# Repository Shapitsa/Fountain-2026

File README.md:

# Fountain-2026
Lutron Competition Submission at SiLab 2026

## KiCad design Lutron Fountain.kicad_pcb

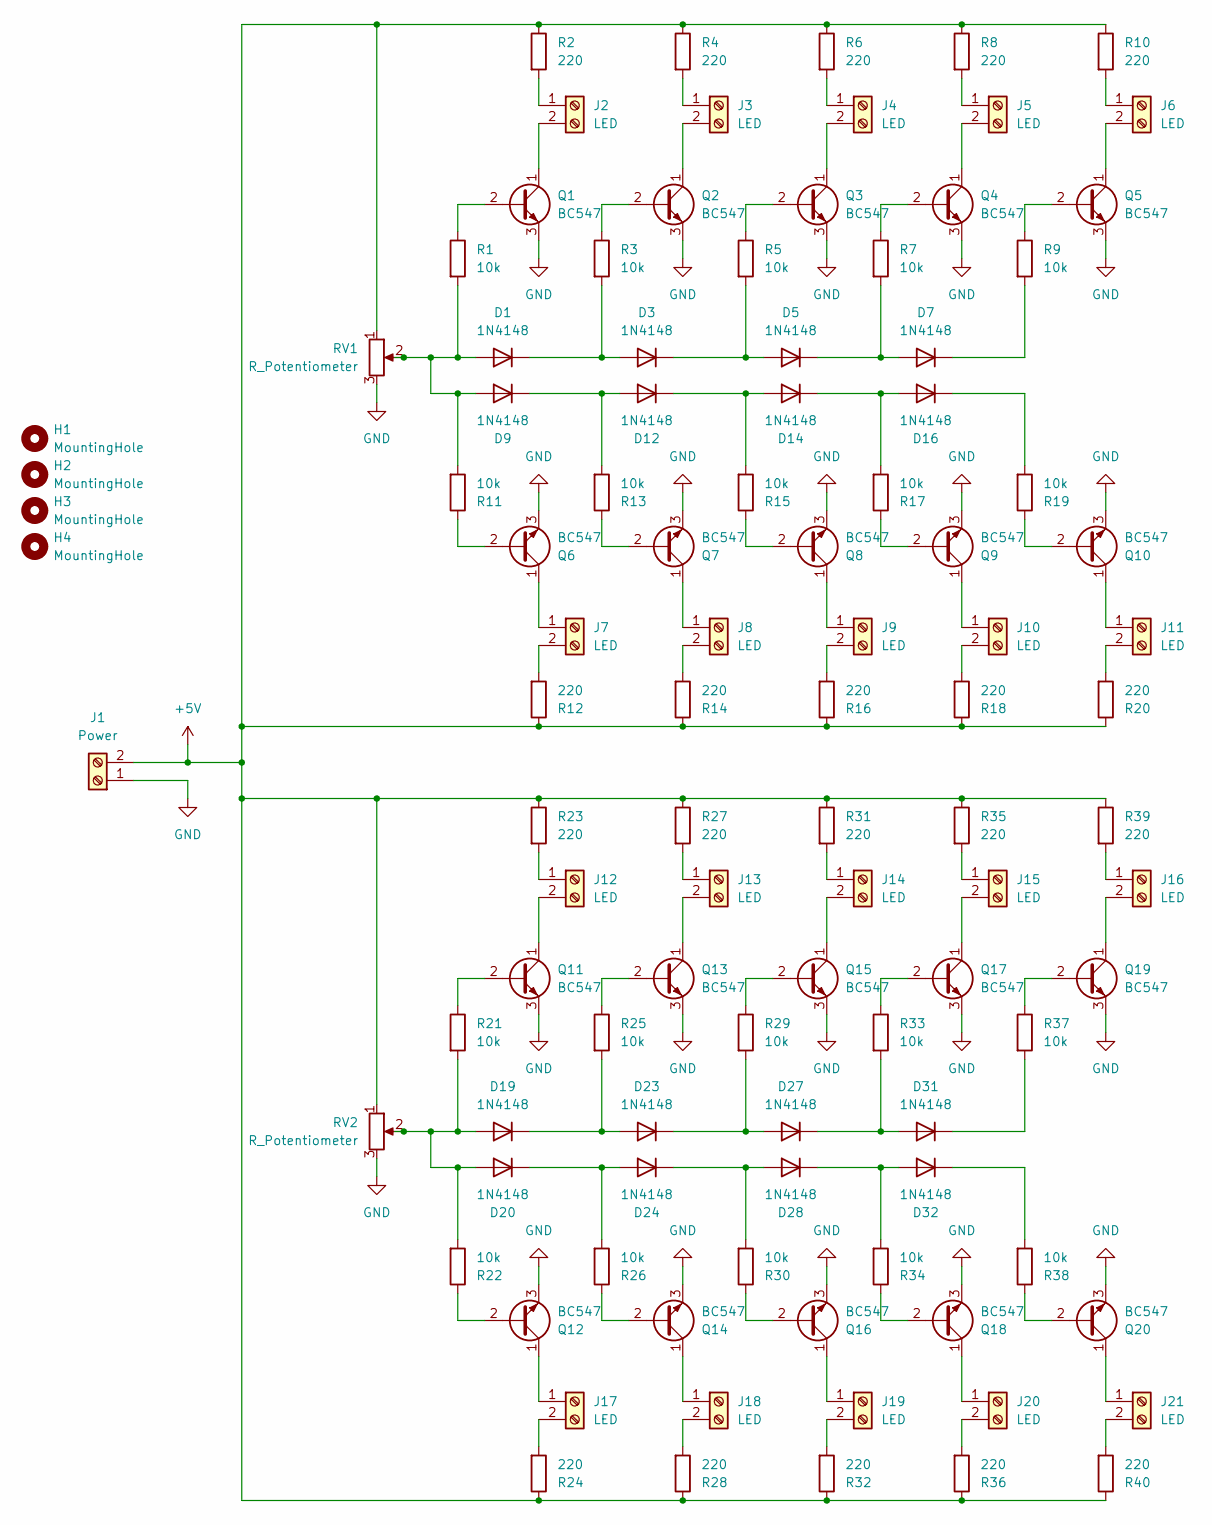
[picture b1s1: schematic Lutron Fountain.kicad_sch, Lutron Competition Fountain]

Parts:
D1, D3, D5, D7, D9, D12, D14, D16, D19, D20, D23, D24, D27, D28, D31, D32: 1N4148; D_DO-35_SOD27_P7.62mm_Horizontal
H1, H2, H3, H4: MountingHole; MountingHole_4.3mm_M4_Pad
J1: Power; TerminalBlock_MaiXu_MX126-5.0-02P_1x02_P5.00mm
J2, J3, J4, J5, J6, J7, J8, J9, J10, J11, J12, J13, J14, J15, J16, J17, J18, J19, J20, J21: LED; TerminalBlock_MaiXu_MX126-5.0-02P_1x02_P5.00mm
Q1, Q2, Q3, Q4, Q5, Q6, Q7, Q8, Q9, Q10, Q11, Q12, Q13, Q14, Q15, Q16, Q17, Q18, Q19, Q20: BC547; TO-92_Inline
R1, R3, R5, R7, R9, R11, R13, R15, R17, R19, R21, R22, R25, R26, R29, R30, R33, R34, R37, R38: 10k; R_Axial_DIN0207_L6.3mm_D2.5mm_P7.62mm_Horizontal
R2, R4, R6, R8, R10, R12, R14, R16, R18, R20, R23, R24, R27, R28, R31, R32, R35, R36, R39, R40: 220; R_Axial_DIN0207_L6.3mm_D2.5mm_P7.62mm_Horizontal
RV1, RV2: R_Potentiometer; Potentiometer_Bourns_3386F_Vertical

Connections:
+5V: J1.2, R2.1, R4.1, R6.1, R8.1, R10.1, R12.1, R14.1, R16.1, R18.1, R20.1, R23.1, R24.1, R27.1, R28.1, R31.1, R32.1, R35.1, R36.1, R39.1, R40.1, RV1.1, RV2.1
GND: J1.1, Q1.3 (E), Q2.3 (E), Q3.3 (E), Q4.3 (E), Q5.3 (E), Q6.3 (E), Q7.3 (E), Q8.3 (E), Q9.3 (E), Q10.3 (E), Q11.3 (E), Q12.3 (E), Q13.3 (E), Q14.3 (E), Q15.3 (E), Q16.3 (E), Q17.3 (E), Q18.3 (E), Q19.3 (E), Q20.3 (E), RV1.3, RV2.3
unnamed: D1.2 (A), D9.2 (A), R1.2, R11.2, RV1.2
unnamed: D1.1 (K), D3.2 (A), R3.2
unnamed: D3.1 (K), D5.2 (A), R5.2
unnamed: D5.1 (K), D7.2 (A), R7.2
unnamed: D7.1 (K), R9.2
unnamed: D9.1 (K), D12.2 (A), R13.2
unnamed: D12.1 (K), D14.2 (A), R15.2
unnamed: D14.1 (K), D16.2 (A), R17.2
unnamed: D16.1 (K), R19.2
unnamed: D19.2 (A), D20.2 (A), R21.2, R22.2, RV2.2
unnamed: D19.1 (K), D23.2 (A), R25.2
unnamed: D20.1 (K), D24.2 (A), R26.2
unnamed: D23.1 (K), D27.2 (A), R29.2
unnamed: D24.1 (K), D28.2 (A), R30.2
unnamed: D27.1 (K), D31.2 (A), R33.2
unnamed: D28.1 (K), D32.2 (A), R34.2
unnamed: D31.1 (K), R37.2
unnamed: D32.1 (K), R38.2
unnamed: J2.1, R2.2
unnamed: J2.2, Q1.1 (C)
unnamed: J3.1, R4.2
unnamed: J3.2, Q2.1 (C)
unnamed: J4.1, R6.2
unnamed: J4.2, Q3.1 (C)
unnamed: J5.1, R8.2
unnamed: J5.2, Q4.1 (C)
unnamed: J6.1, R10.2
unnamed: J6.2, Q5.1 (C)
unnamed: J7.1, Q6.1 (C)
unnamed: J7.2, R12.2
unnamed: J8.1, Q7.1 (C)
unnamed: J8.2, R14.2
unnamed: J9.1, Q8.1 (C)
unnamed: J9.2, R16.2
unnamed: J10.1, Q9.1 (C)
unnamed: J10.2, R18.2
unnamed: J11.1, Q10.1 (C)
unnamed: J11.2, R20.2
unnamed: J12.1, R23.2
unnamed: J12.2, Q11.1 (C)
unnamed: J13.1, R27.2
unnamed: J13.2, Q13.1 (C)
unnamed: J14.1, R31.2
unnamed: J14.2, Q15.1 (C)
unnamed: J15.1, R35.2
unnamed: J15.2, Q17.1 (C)
unnamed: J16.1, R39.2
unnamed: J16.2, Q19.1 (C)
unnamed: J17.1, Q12.1 (C)
unnamed: J17.2, R24.2
unnamed: J18.1, Q14.1 (C)
unnamed: J18.2, R28.2
unnamed: J19.1, Q16.1 (C)
unnamed: J19.2, R32.2
unnamed: J20.1, Q18.1 (C)
unnamed: J20.2, R36.2
unnamed: J21.1, Q20.1 (C)
unnamed: J21.2, R40.2
unnamed: Q1.2 (B), R1.1
unnamed: Q2.2 (B), R3.1
unnamed: Q3.2 (B), R5.1
unnamed: Q4.2 (B), R7.1
unnamed: Q5.2 (B), R9.1
unnamed: Q6.2 (B), R11.1
unnamed: Q7.2 (B), R13.1
unnamed: Q8.2 (B), R15.1
unnamed: Q9.2 (B), R17.1
unnamed: Q10.2 (B), R19.1
unnamed: Q11.2 (B), R21.1
unnamed: Q12.2 (B), R22.1
unnamed: Q13.2 (B), R25.1
unnamed: Q14.2 (B), R26.1
unnamed: Q15.2 (B), R29.1
unnamed: Q16.2 (B), R30.1
unnamed: Q17.2 (B), R33.1
unnamed: Q18.2 (B), R34.1
unnamed: Q19.2 (B), R37.1
unnamed: Q20.2 (B), R38.1

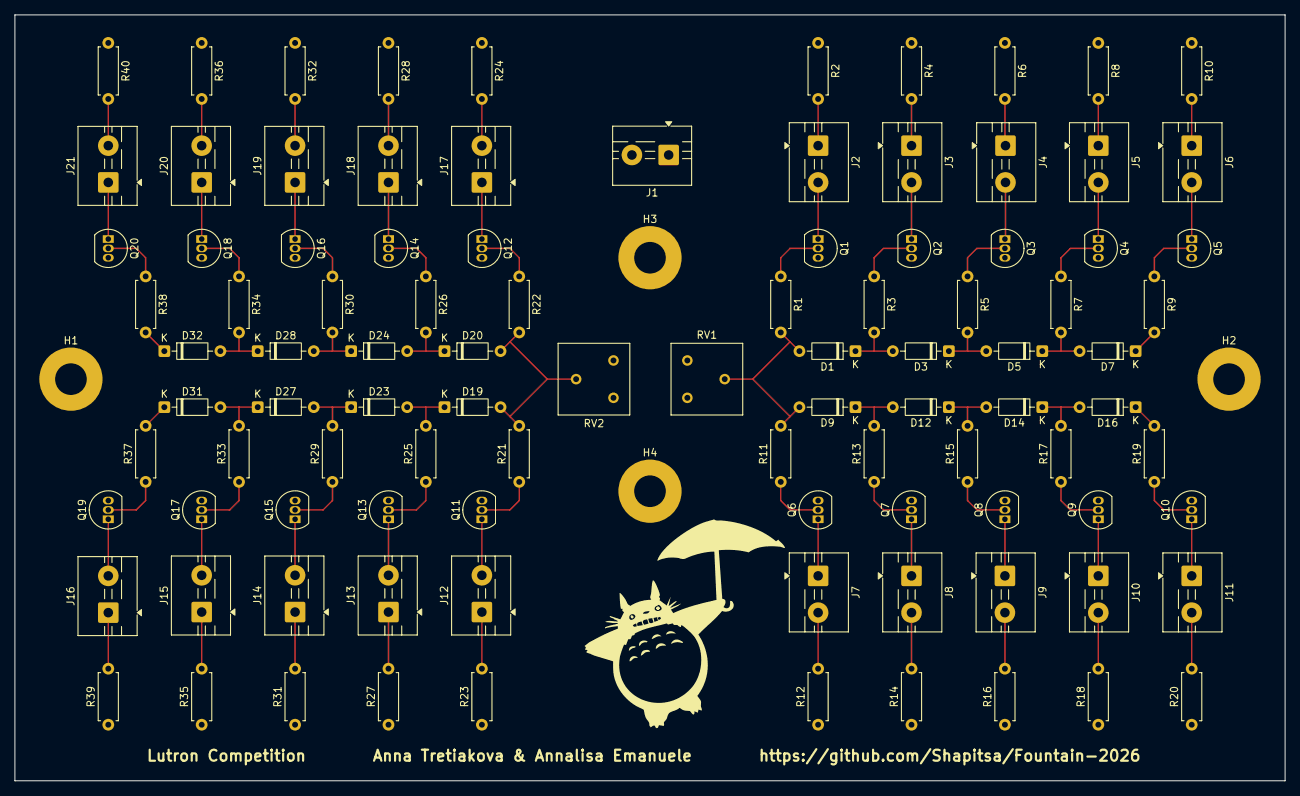
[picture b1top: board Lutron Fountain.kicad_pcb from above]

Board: 4 copper layers, 172.7 x 104.1 mm, 103 parts (0 on the bottom side), 80 nets.

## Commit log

2026-01-24 Initial connection to git
2026-01-24 Initial connection to giyhub
2026-01-24 commit two
2026-01-24 addition three
2026-01-24 schematic done
2026-01-26 pcb finished
2026-01-28 made shared gnd
2026-01-29 added gnd and power
2026-01-29 finalized pcb
2026-02-02 finalized
2026-02-02 final
